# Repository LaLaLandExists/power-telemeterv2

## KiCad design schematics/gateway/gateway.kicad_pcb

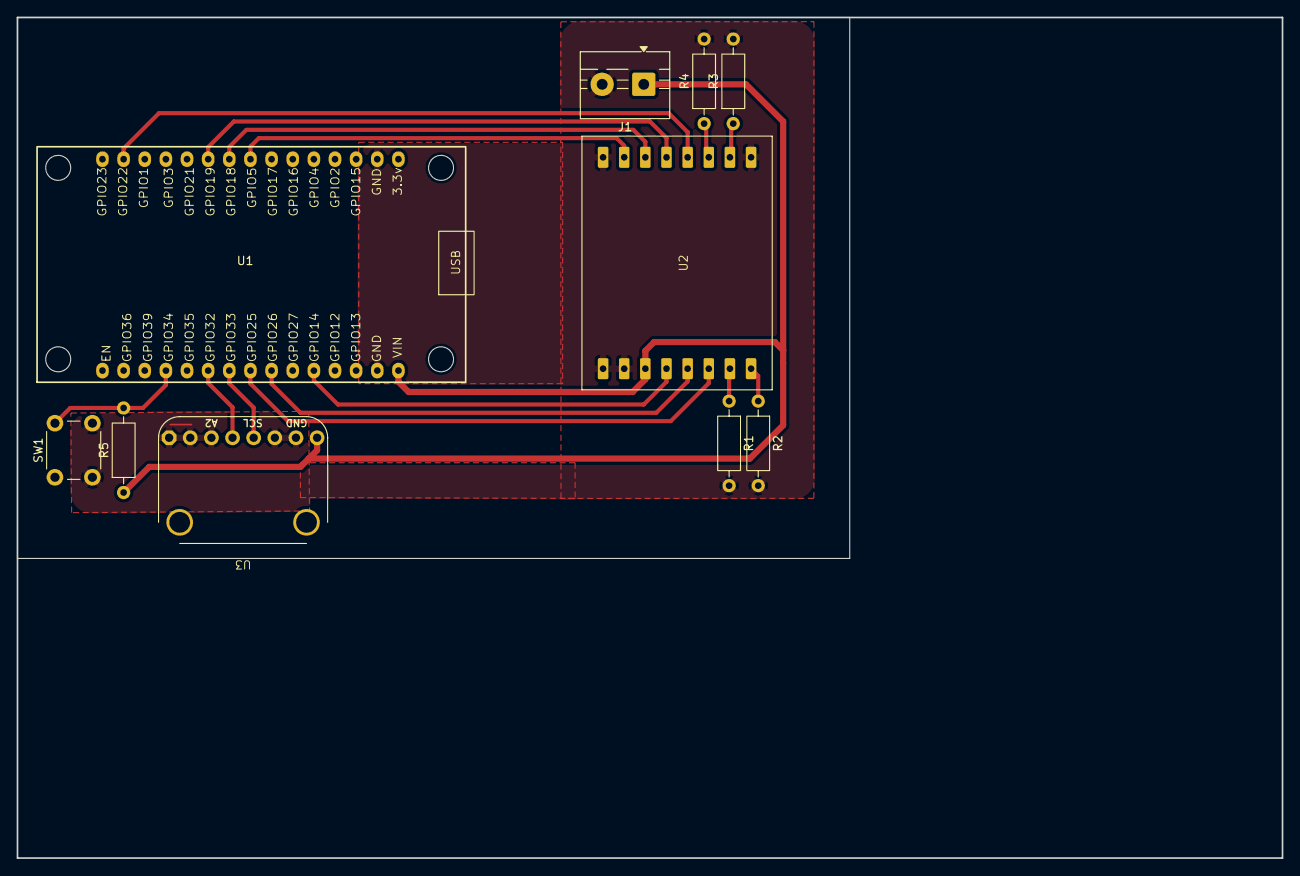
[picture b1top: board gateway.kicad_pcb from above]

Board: 2 copper layers, 152.0 x 101.0 mm, 10 parts (0 on the bottom side), 16 nets.

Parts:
J1: Power; TerminalBlock_MaiXu_MX126-5.0-02P_1x02_P5.00mm
R1, R2, R3, R4, R5: 10k; R_Axial_DIN0207_L6.3mm_D2.5mm_P10.16mm_Horizontal
SW1: SW_Push; SW_PUSH_6mm
U1: ESP32_30pin
U2: LoRa-02
U3: frami2c

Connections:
3V3: J1.1, R5.1, U1.1 (VIN), U2.2 (3V3), U3.8 (VCC)
/FRAM_SCL: U1.9 (GPIO33), U3.5 (SCL)
/FRAM_SDA: U1.10 (GPIO32), U3.4 (SDA)
/LoRa_DIO0: U1.7 (GPIO26), U2.4 (DIO0)
/LoRa_DIO1: U1.8 (GPIO25), U2.5 (DIO1)
/LoRa_MISO: U1.25 (GPIO19), U2.12 (MISO)
/LoRa_MOSI: U1.24 (GPIO18), U2.11 (MOSI)
/LoRa_NSS: U1.23 (GPIO5), U2.10 (NSS)
/LoRa_RST: U1.5 (GPIO14), U2.3 (RST)
/LoRa_SCK: U1.29 (GPIO22), U2.13 (SCK)
GND: J1.2, R1.2, R2.2, R3.2, R4.2, SW1.2, U1.2 (GND), U1.17 (GND), U2.1 (GND), U3.1 (A0), U3.2 (A1), U3.3 (A2), U3.6 (WP), U3.7 (GND)
unnamed: R5.2, SW1.1, U1.12 (GPIO34)
unnamed: R1.1, U2.6 (DIO2)
unnamed: R2.1, U2.7 (DIO3)
unnamed: R3.1, U2.8 (DIO4)
unnamed: R4.1, U2.9 (DIO5)

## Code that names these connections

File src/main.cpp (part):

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 * -- Hardware ------------------------------------------------------------------
 *
 *   SX1278 (VSPI - identical on both roles):
 *     NSS  -> GPIO5    SCK  -> GPIO21
 *     MISO -> GPIO19   MOSI -> GPIO18
 *     DIO0 -> GPIO14   RST  -> GPIO13
 *     DIO1 -> GPIO27 (tie to GND if unused)
 *
 *   Gateway only:
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 *     Dashboard: http://telemeter.local  or  http://192.168.4.1
 *
 *   Node only:
 *     PZEM-004T v3  -> Serial2  PZEM_RX=GPIO22, PZEM_TX=GPIO23
 *     Relay signal  -> GPIO25 (active HIGH)
 *     LED green     -> GPIO32
 *     LED red       -> GPIO33
 */

// --- Macro resolution ---------------------------------------------------------
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
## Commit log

2026-03-24 migrate to github
2026-04-15 added schematics and adjusted pins
2026-05-04 AP-STA fix + fake pzem mode
    fix task starvation issue which prevented tasks from executing. create a testing module for LoRa connectivity
2026-05-05 add pcb pdf for both telemetry and gateway nodes
